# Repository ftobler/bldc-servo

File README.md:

# BLDC Servo

Custom PCB with BLDC controller for a Servo.

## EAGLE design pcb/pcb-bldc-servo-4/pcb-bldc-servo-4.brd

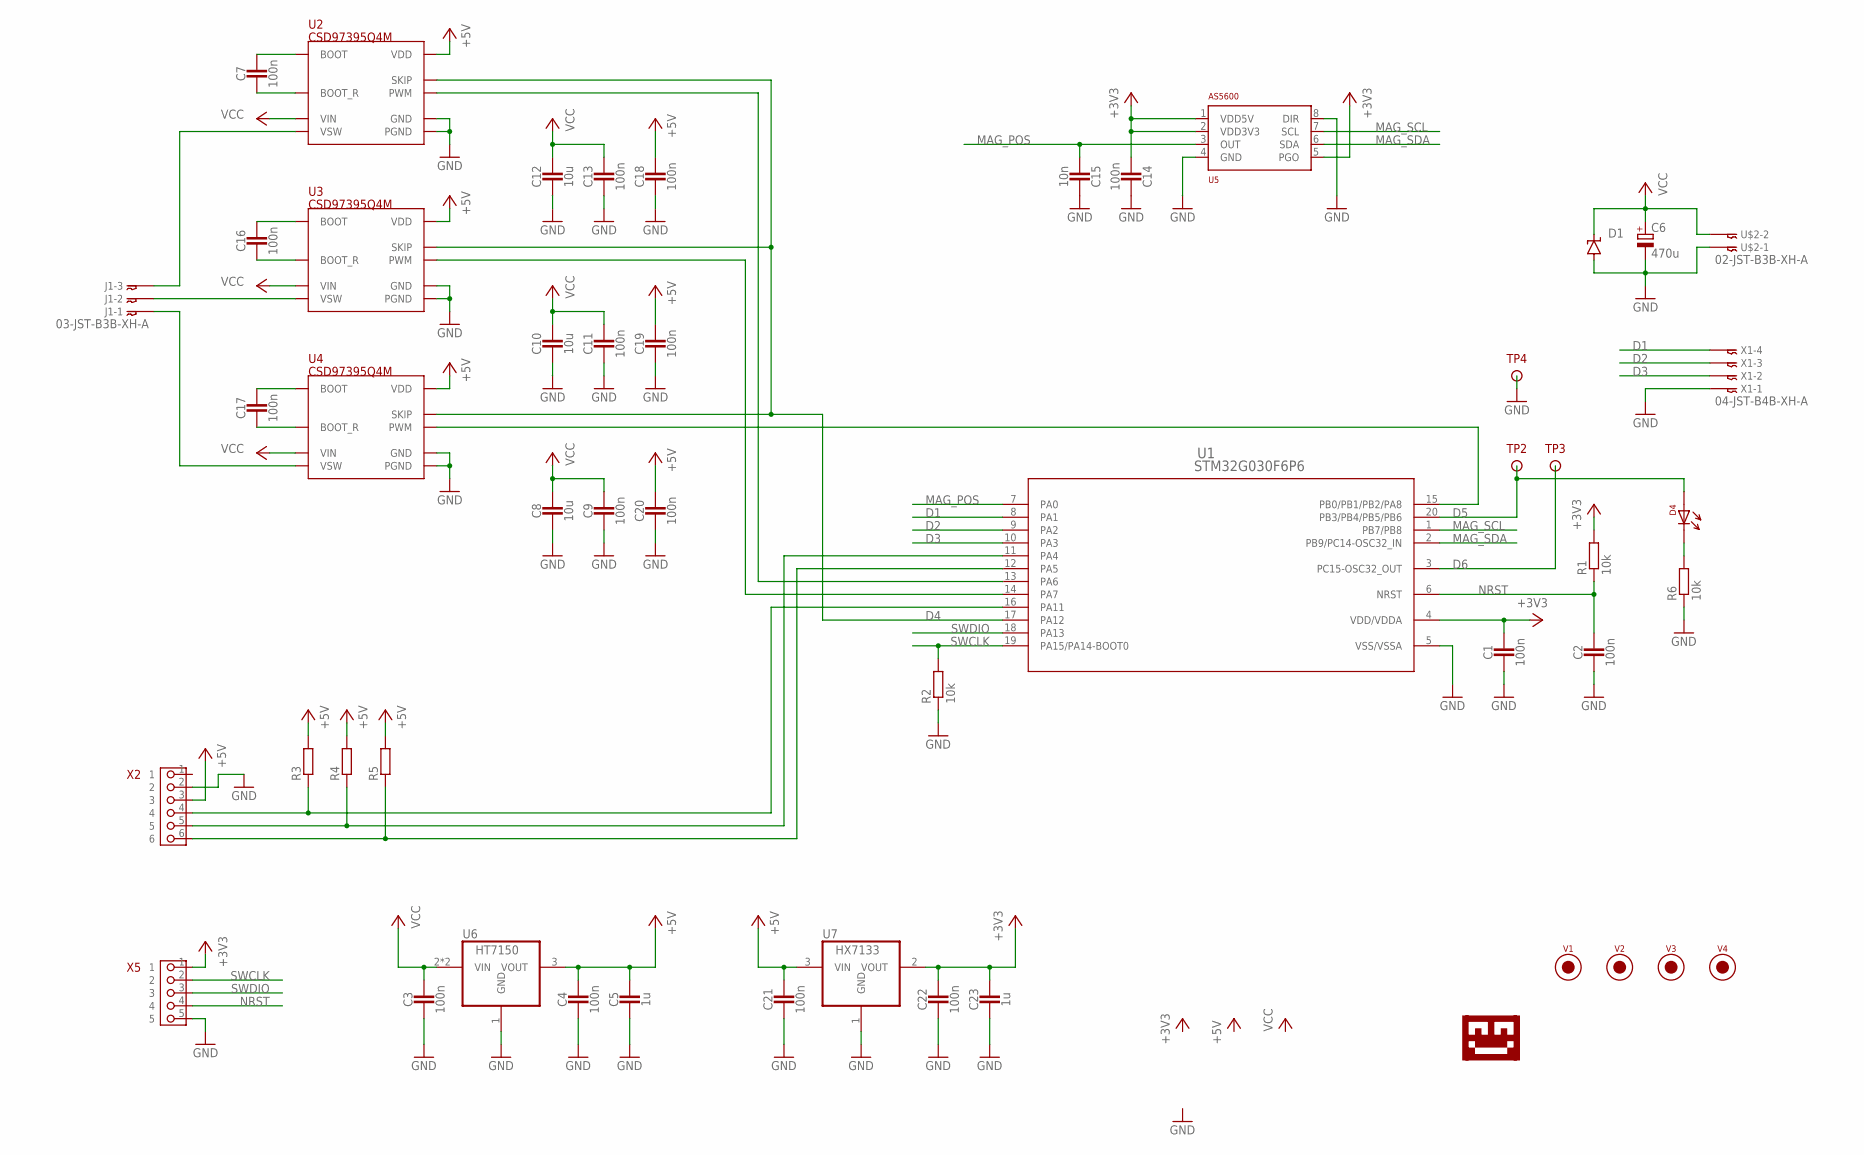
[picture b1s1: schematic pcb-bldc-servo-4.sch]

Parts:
C1, C2, C3, C4, C7, C9, C11, C13, C14, C16, C17, C18, C19, C20, C21, C22: 100n; 0603_CAP
C5, C23: 1u; 0603_CAP
C6: 470u; 153CLV-1010
C8, C10, C12: 10u; 1206_CAP
C15: 10n; 0603_CAP
D1: SUPPRESSOR-SMBJ; SMBJ
D4: LED-0805; 0805-DOT
J1: 03-JST-B3B-XH-A; B3B-XH
R1, R2, R6: 10k; 0603-RES
R3, R4, R5: RESISTOR0603_RES; 0603-RES
TP2, TP3, TP4: TESTPIN1MM; PIN-SMD-1X1-TEST_1M0
U1: STM32G030F6P6; TSSOP20
U2, U3, U4: CSD97395Q4M
U5: AS5600; SOIC-8
U6: HT7150; SOT-89
U7: HX7133; SOT-23
U$1: LOGO-TOBENG-1MM-FINISH; TOBENG-1MM-FINISH
U$2: 02-JST-B3B-XH-A; B2B-XH
V1, V2, V3, V4: FIDUCIAL2MM; FIDUCIAL_2MM
X1: 04-JST-B4B-XH-A; B4B-XH
X2: PIN_6X1; PIN_6X1_MOLEX_PICOBLADE
X5: PIN_5X1HD; PIN_5X1_HD

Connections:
+3V3: C1.1, C14.1, C22.1, C23.1, R1.2, U1.4 (VDD/VDDA), U5.1 (VDD5V), U5.2 (VDD3V3), U5.5 (PGO), U7.2 (VOUT), X5.1
+5V: C4.1, C5.1, C18.1, C19.1, C20.1, C21.1, R3.2, R4.2, R5.2, U2.VDD, U2.VDD1 (VDD), U3.VDD, U3.VDD1 (VDD), U4.VDD, U4.VDD1 (VDD), U6.3 (VOUT), U7.3 (VIN), X2.3
D1: U1.8 (PA1), X1.P$4
D2: U1.9 (PA2), X1.P$3
D3: U1.10 (PA3), X1.P$2
D4: U1.17 (PA12), U2.SKIP, U2.SKIP1 (SKIP), U3.SKIP, U3.SKIP1 (SKIP), U4.SKIP, U4.SKIP1 (SKIP)
D5: D4.1, TP2.1, U1.20 (PB3/PB4/PB5/PB6)
D6: TP3.1, U1.3 (PC15-OSC32_OUT)
GND: C1.2, C2.2, C3.2, C4.2, C5.2, C6.-, C8.2, C9.2, C10.2, C11.2, C12.2, C13.2, C14.2, C15.2, C18.2, C19.2, C20.2, C21.2, C22.2, C23.2, D1.A, R2.1, R6.1, TP4.1, U1.5 (VSS/VSSA), U2.GND, U2.GND1 (GND), U2.PGND, U3.GND, U3.GND1 (GND), U3.PGND, U4.GND, U4.GND1 (GND), U4.PGND, U5.4 (GND), U5.8 (DIR), U6.1 (GND), U7.1 (GND), U$2.P$1, X1.P$1, X2.2, X5.5
MAG_POS: C15.1, U1.7 (PA0), U5.3 (OUT)
MAG_SCL: U1.1 (PB7/PB8), U5.7 (SCL)
MAG_SDA: U1.2 (PB9/PC14-OSC32_IN), U5.6 (SDA)
unnamed: C7.1, U2.BOOT, U2.BOOT1 (BOOT)
unnamed: C7.2, U2.BOOT_R, U2.BOOT_R1 (BOOT_R)
unnamed: J1.P$2, U3.VSW, U3.VSW1 (VSW), U3.VSW2 (VSW), U3.VSW3 (VSW), U3.VSW4 (VSW), U3.VSW5 (VSW), U3.VSW6 (VSW)
unnamed: J1.P$3, U2.VSW, U2.VSW1 (VSW), U2.VSW2 (VSW), U2.VSW3 (VSW), U2.VSW4 (VSW), U2.VSW5 (VSW), U2.VSW6 (VSW)
unnamed: U1.13 (PA6), U2.PWM, U2.PWM1 (PWM)
unnamed: U1.14 (PA7), U3.PWM, U3.PWM1 (PWM)
unnamed: J1.P$1, U4.VSW, U4.VSW1 (VSW), U4.VSW2 (VSW), U4.VSW3 (VSW), U4.VSW4 (VSW), U4.VSW5 (VSW), U4.VSW6 (VSW)
unnamed: C16.1, U3.BOOT, U3.BOOT1 (BOOT)
unnamed: U1.15 (PB0/PB1/PB2/PA8), U4.PWM, U4.PWM1 (PWM)
unnamed: C16.2, U3.BOOT_R, U3.BOOT_R1 (BOOT_R)
unnamed: C17.1, U4.BOOT, U4.BOOT1 (BOOT)
unnamed: C17.2, U4.BOOT_R, U4.BOOT_R1 (BOOT_R)
unnamed: D4.2, R6.2
unnamed: R5.1, U1.12 (PA5), X2.6
unnamed: R4.1, U1.11 (PA4), X2.5
unnamed: R3.1, U1.16 (PA11), X2.4
NRST: C2.1, R1.1, U1.6 (NRST), X5.4
SWCLK: R2.2, U1.19 (PA15/PA14-BOOT0), X5.2
SWDIO: U1.18 (PA13), X5.3
VCC: C3.1, C6.+, C8.1, C9.1, C10.1, C11.1, C12.1, C13.1, D1.C, U2.VIN, U2.VIN1 (VIN), U2.VIN2 (VIN), U2.VIN3 (VIN), U2.VIN4 (VIN), U2.VIN5 (VIN), U2.VIN6 (VIN), U3.VIN, U3.VIN1 (VIN), U3.VIN2 (VIN), U3.VIN3 (VIN), U3.VIN4 (VIN), U3.VIN5 (VIN), U3.VIN6 (VIN), U4.VIN, U4.VIN1 (VIN), U4.VIN2 (VIN), U4.VIN3 (VIN), U4.VIN4 (VIN), U4.VIN5 (VIN), U4.VIN6 (VIN), U6.2 (VIN), U6.2@1 (VIN), U$2.P$2

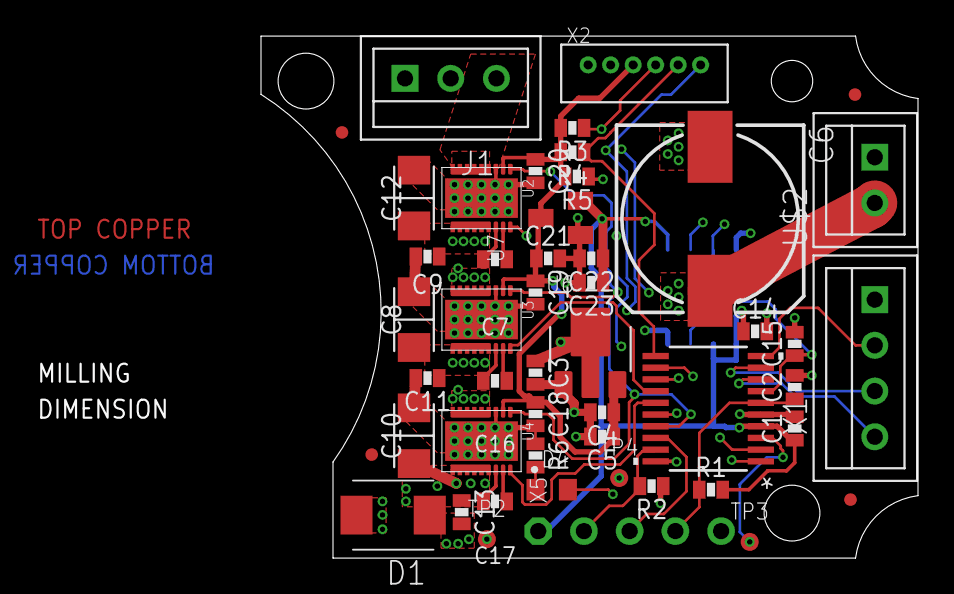
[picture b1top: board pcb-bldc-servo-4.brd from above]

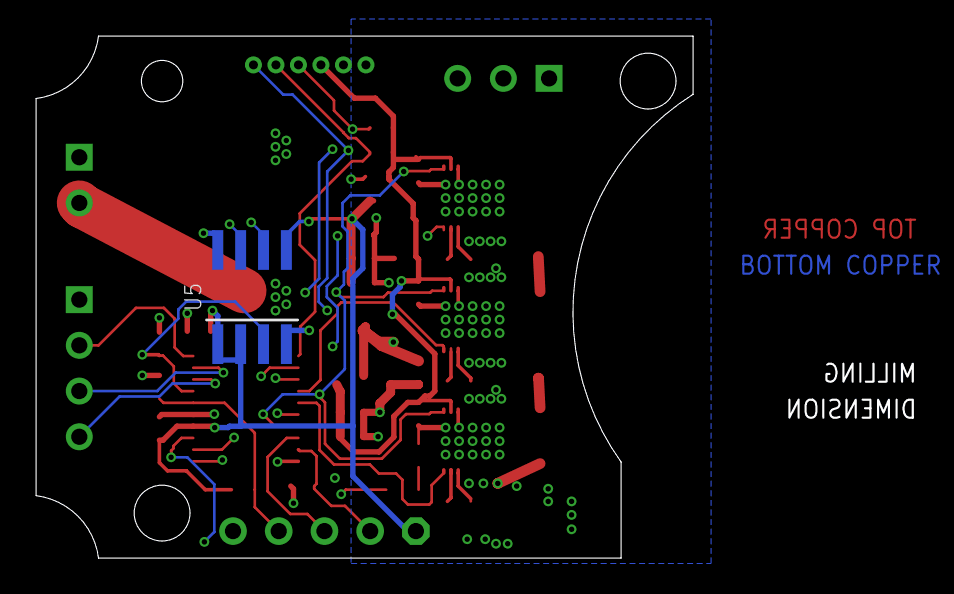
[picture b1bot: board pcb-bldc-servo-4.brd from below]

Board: 4 copper layers, 36.5 x 29.0 mm, 51 parts (2 on the bottom side), 32 nets.

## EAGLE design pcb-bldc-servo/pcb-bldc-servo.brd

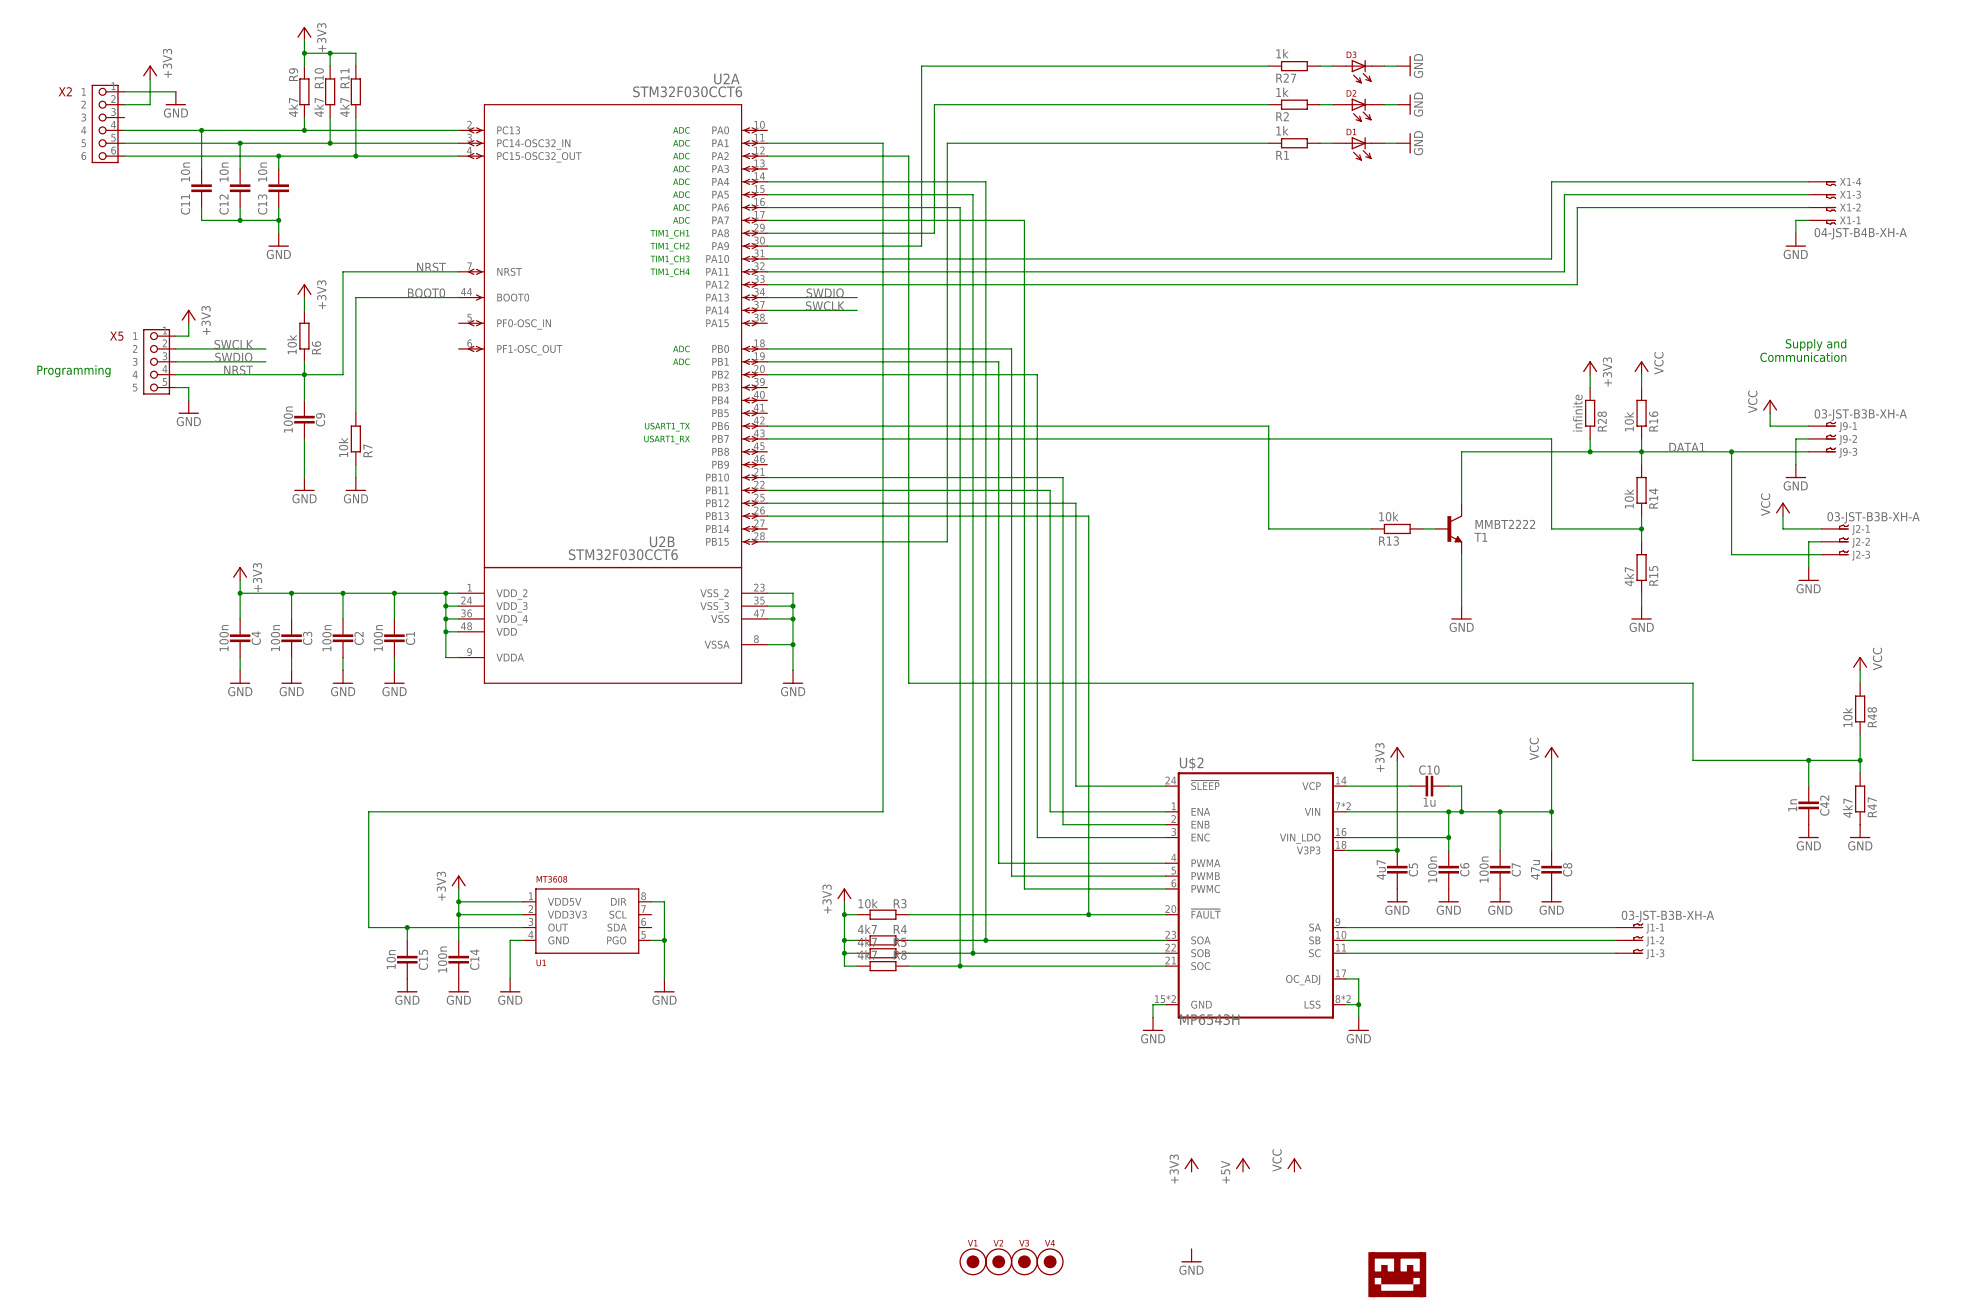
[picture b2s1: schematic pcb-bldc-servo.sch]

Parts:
C1, C2, C3, C4, C6, C7, C9, C14: 100n; 0603_CAP
C5: 4u7; 0805_CAP
C8: 47u; 1210_CAP
C10: 1u; 0603_CAP
C11, C12, C13, C15: 10n; 0603_CAP
C42: 1n; 0603_CAP
D1, D2, D3: LED-0805; 0805-DOT
J1, J2, J9: 03-JST-B3B-XH-A; B3B-XH
R1, R2, R27: 1k; 0603-RES
R3, R6, R7, R13, R14, R16, R48: 10k; 0603-RES
R4, R5, R8, R9, R10, R11, R15, R47: 4k7; 0603-RES
R28: infinite; 0603-RES
T1: MMBT2222; SOT23-BEC
U1: AS5600; SOIC-8
U2: STM32F030CCT6; LQFP48-7X7MM
U$1: LOGO-TOBENG-1MM-FINISH; TOBENG-1MM-FINISH
U$2: MP6543H; QFN24
V1, V2, V3, V4: FIDUCIAL2MM; FIDUCIAL_2MM
X1: 04-JST-B4B-XH-A; B4B-XH
X2: PIN_6X1; PIN_6X1_MOLEX_PICOBLADE
X5: PIN_5X1HD; PIN_5X1_HD

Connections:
BOOT0: R7.2, U2.44 (BOOT0)
DATA1: J2.P$3, J9.P$3, R14.2, R16.1, R28.1, T1.C
M3B1: C42.1, R47.2, R48.1, U2.12 (PA2)
unnamed: U2.20 (PB2), U$2.3 (ENC)
unnamed: U2.21 (PB10), U$2.2 (ENB)
unnamed: U2.22 (PB11), U$2.1 (ENA)
unnamed: D1.1, R1.2
unnamed: U2.17 (PA7), U$2.6 (PWMC)
unnamed: U2.18 (PB0), U$2.5 (PWMB)
unnamed: D2.1, R2.2
unnamed: R27.1, U2.30 (PA9)
unnamed: U2.19 (PB1), U$2.4 (PWMA)
unnamed: R2.1, U2.29 (PA8)
unnamed: D3.1, R27.2
unnamed: R13.1, U2.42 (PB6)
unnamed: R14.1, R15.2, U2.43 (PB7)
unnamed: R13.2, T1.B
unnamed: J1.P$1, U$2.9 (SA)
unnamed: J1.P$2, U$2.10 (SB)
unnamed: J1.P$3, U$2.11 (SC)
unnamed: R8.1, U2.16 (PA6), U$2.21 (SOC)
unnamed: R5.1, U2.15 (PA5), U$2.22 (SOB)
unnamed: R4.1, U2.14 (PA4), U$2.23 (SOA)
unnamed: U2.25 (PB12), U$2.24 (!SLEEP)
unnamed: R3.1, U2.26 (PB13), U$2.20 (!FAULT)
unnamed: U2.33 (PA12), X1.P$2
unnamed: C13.1, R11.2, U2.4 (PC15-OSC32_OUT), X2.6
unnamed: C12.1, R10.2, U2.3 (PC14-OSC32_IN), X2.5
unnamed: R1.1, U2.28 (PB15)
unnamed: C10.1, U$2.14 (VCP)
unnamed: C11.1, R9.2, U2.2 (PC13), X2.4
unnamed: U2.32 (PA11), X1.P$3
unnamed: U2.31 (PA10), X1.P$4
unnamed 33: U2.40 (PB4); also elsewhere on the board
unnamed 34: C15.1, U1.3 (OUT), U2.11 (PA1); also elsewhere on the board
unnamed 35: U2.41 (PB5); also elsewhere on the board
unnamed 36: U2.13 (PA3); also elsewhere on the board
unnamed 37: U2.10 (PA0); also elsewhere on the board
NRST: C9.1, R6.1, U2.7 (NRST), X5.4
SWCLK: U2.37 (PA14), X5.2
SWDIO: U2.34 (PA13), X5.3
VCC: C6.1, C7.1, C8.1, C10.2, J2.P$1, J9.P$1, R16.2, R48.2, U$2.7 (VIN), U$2.13 (VIN), U$2.16 (VIN_LDO)

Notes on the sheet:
Programming
ADC
TIM1_CH1
TIM1_CH2
TIM1_CH3
TIM1_CH4
USART1_RX
USART1_TX
Supply and Communication

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
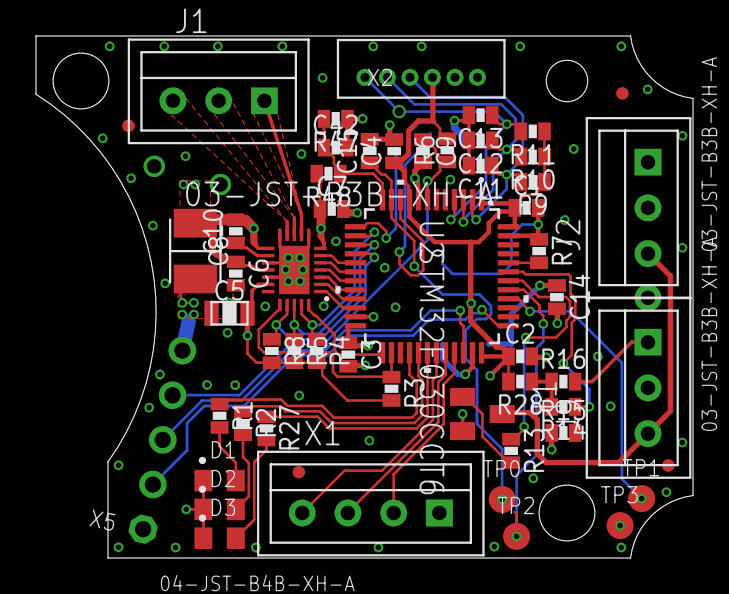
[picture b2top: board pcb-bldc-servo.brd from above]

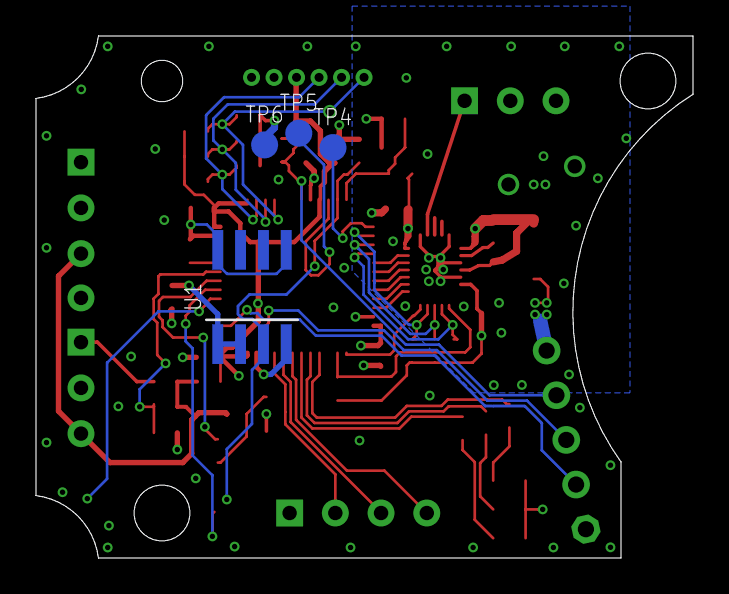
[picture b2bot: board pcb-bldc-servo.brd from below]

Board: 4 copper layers, 36.5 x 29.0 mm, 60 parts (5 on the bottom side), 44 nets.

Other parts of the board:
TP0, TP1, TP2, TP3, TP4, TP5, TP6: TESTPIN; PIN-SMD-1X1-TEST_1M5

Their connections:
unnamed 33: TP1.1; also elsewhere on the board
unnamed 34: TP0.1; also elsewhere on the board
unnamed 35: TP2.1; also elsewhere on the board
unnamed 36: TP4.1; also elsewhere on the board
unnamed 37: TP5.1; also elsewhere on the board

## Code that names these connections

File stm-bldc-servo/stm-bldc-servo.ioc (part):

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Mcu.Name=STM32G030F6Px
Mcu.Package=TSSOP20
Mcu.UserName=STM32G030F6Px
PA0.GPIOParameters=GPIO_Label
PA0.GPIO_Label=ADC1_IN0_MAG_POS
PA0.Mode=IN0
PA0.Signal=ADC1_IN0
PA11\ [PA9].GPIOParameters=GPIO_Label
PA11\ [PA9].GPIO_Label=SENS1
PA11\ [PA9].Signal=GPIO_Input
PA12\ [PA10].GPIOParameters=GPIO_Label
PA12\ [PA10].GPIO_Label=SKIP
PA12\ [PA10].Signal=GPIO_Output
PA13.Mode=Serial_Wire
PA13.Signal=SYS_SWDIO
PA14-BOOT0.Mode=Serial_Wire
PA14-BOOT0.Signal=SYS_SWCLK
PA14-BOOT0__PA15.StandardMode=true
PA2.Mode=Asynchronous
PA2.Signal=USART2_TX
PA3.Mode=Asynchronous
PA3.Signal=USART2_RX
PA4.GPIOParameters=GPIO_Label
PA4.GPIO_Label=SENS3
PA4.Signal=GPIO_Input
PA5.GPIOParameters=GPIO_Label
PA5.GPIO_Label=SENS2
PA5.Signal=GPIO_Input
PA6.Signal=S_TIM3_CH1
PA7.Signal=S_TIM3_CH2
PB0.Signal=S_TIM3_CH3
PB0__PB1__PB2__PA8.StandardMode=true
PB3.GPIOParameters=GPIO_Label
PB3.GPIO_Label=LED
PB3.Signal=GPIO_Output
PB3__PB4__PB5__PB6.StandardMode=true
PB7__PB8.StandardMode=true
PB8.GPIOParameters=GPIO_Pu
PB8.GPIO_Pu=GPIO_PULLUP
PB8.Mode=I2C
PB8.Signal=I2C1_SCL
PB9.GPIOParameters=GPIO_Pu
PB9.GPIO_Pu=GPIO_PULLUP
PB9.Mode=I2C
PB9.Signal=I2C1_SDA
PC14-OSC32_IN\ (PC14)__PB9.StandardMode=true
RCC.HSE_VALUE=8000000
RCC.SYSCLKFreq_VALUE=64000000
RCC.SYSCLKSource=RCC_SYSCLKSOURCE_PLLCLK
board=custom

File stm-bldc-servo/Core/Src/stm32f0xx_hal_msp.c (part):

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
    __HAL_RCC_GPIOA_CLK_ENABLE();
    /**ADC GPIO Configuration
    PA1     ------> ADC_IN1
    PA2     ------> ADC_IN2
    PA4     ------> ADC_IN4
    PA5     ------> ADC_IN5
    PA6     ------> ADC_IN6
    */
    GPIO_InitStruct.Pin = ADC_ENCODER_Pin|ADC_VOLT_Pin|ADC_I1_Pin|ADC_I2_Pin
                          |ADC_I3_Pin;
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    __HAL_RCC_ADC1_CLK_DISABLE();

    /**ADC GPIO Configuration
    PA1     ------> ADC_IN1
    PA2     ------> ADC_IN2
    PA4     ------> ADC_IN4
    PA5     ------> ADC_IN5
    PA6     ------> ADC_IN6
    */
    HAL_GPIO_DeInit(GPIOA, ADC_ENCODER_Pin|ADC_VOLT_Pin|ADC_I1_Pin|ADC_I2_Pin
                          |ADC_I3_Pin);
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    __HAL_RCC_GPIOA_CLK_ENABLE();
    __HAL_RCC_GPIOB_CLK_ENABLE();
    /**TIM3 GPIO Configuration
    PA7     ------> TIM3_CH2
    PB0     ------> TIM3_CH3
    PB1     ------> TIM3_CH4
    */
    GPIO_InitStruct.Pin = GPIO_PIN_7;
    GPIO_InitStruct.Mode = GPIO_MODE_AF_PP;
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
    __HAL_RCC_GPIOB_CLK_ENABLE();
    /**USART1 GPIO Configuration
    PB6     ------> USART1_TX
    PB7     ------> USART1_RX
    */
    GPIO_InitStruct.Pin = GPIO_PIN_6|GPIO_PIN_7;
    GPIO_InitStruct.Mode = GPIO_MODE_AF_PP;
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    __HAL_RCC_USART1_CLK_DISABLE();

    /**USART1 GPIO Configuration
    PB6     ------> USART1_TX
    PB7     ------> USART1_RX
    */
    HAL_GPIO_DeInit(GPIOB, GPIO_PIN_6|GPIO_PIN_7);

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
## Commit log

2022-09-07 pcb outline
2022-09-07 eagle pcbs
2022-09-07 outline
2022-09-07 step file
2022-09-07 gerber
2022-09-07 readme
2022-09-07 datasheet and readme
2022-09-07 rename image
2022-09-08 gitignore
2022-09-08 updated gerber
2022-09-08 move to root
2022-09-08 created project
2024-04-01 updated schematic for correct sensor cable
2024-04-01 motor datasheet
2024-04-01 redesign with new driver
2024-04-02 productpictures i found
2024-04-02 sensor datasheet
2024-04-02 small fixes
2024-04-02 board revision 3
2024-04-02 export file
2024-04-17 pcb v3 as ordered - moved to pcb folder
2024-04-17 stm32 project with new processor
2024-04-17 datasheet of driver
2024-04-17 very simple control loop
2024-04-18 rtos / control loop
2024-04-18 cleanup / control loop / pwm to 20kHz
2024-04-18 indent
2024-04-18 typo
2024-04-19 i2c sensor, modbus
2024-04-20 re-order tasks
2024-04-20 bootup
2024-04-20 accel mapping
2024-05-10 second LDO for 3.3 and 5V separate
2024-06-11 pcb release v4
2024-06-11 flortos optimize fix

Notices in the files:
stm-bldc-servo/Core/Src/stm32f0xx_hal_msp.c:
Copyright (c) 2022 STMicroelectronics.
All rights reserved.
This software is licensed under terms that can be found in the LICENSE file
parts and their libraries:
COPYRIGHT: Copyright (C) 2018 Accelerated Designs. All rights reserved
COPYRIGHT: Copyright (C) 2024 Ultra Librarian. All rights reserved.
